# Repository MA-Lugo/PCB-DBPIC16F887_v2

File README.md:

# PCB-DBPIC16F887_v2
Development Board based on Microchip PIC16F887 8-Bit MCU

_Tarjeta de desarrollo basada en PIC16F887 (sistema mínimo)_

## Comenzando 🚀
### Pre-requisitos 📋

* Autodesk Eagle

## Wiki 📖

Puedes encontrar el esquemático [aquí.](https://drive.google.com/uc?export=view&id=1uyhpvZt8SFJf6NlxQCLjJcooKPEDv15b)

Tambíen puedes ver una animación [aquí.](https://drive.google.com/file/d/1NO_eVydhyPA-O2Zp3BOySrAR04YveleB/view?usp=sharing)

## Lista de Componentes 📖

## Ensable 🛠️

## Autor ✒️

* **Mario A. Lugo**  [MA-Lugo](https://github.com/MA-Lugo)

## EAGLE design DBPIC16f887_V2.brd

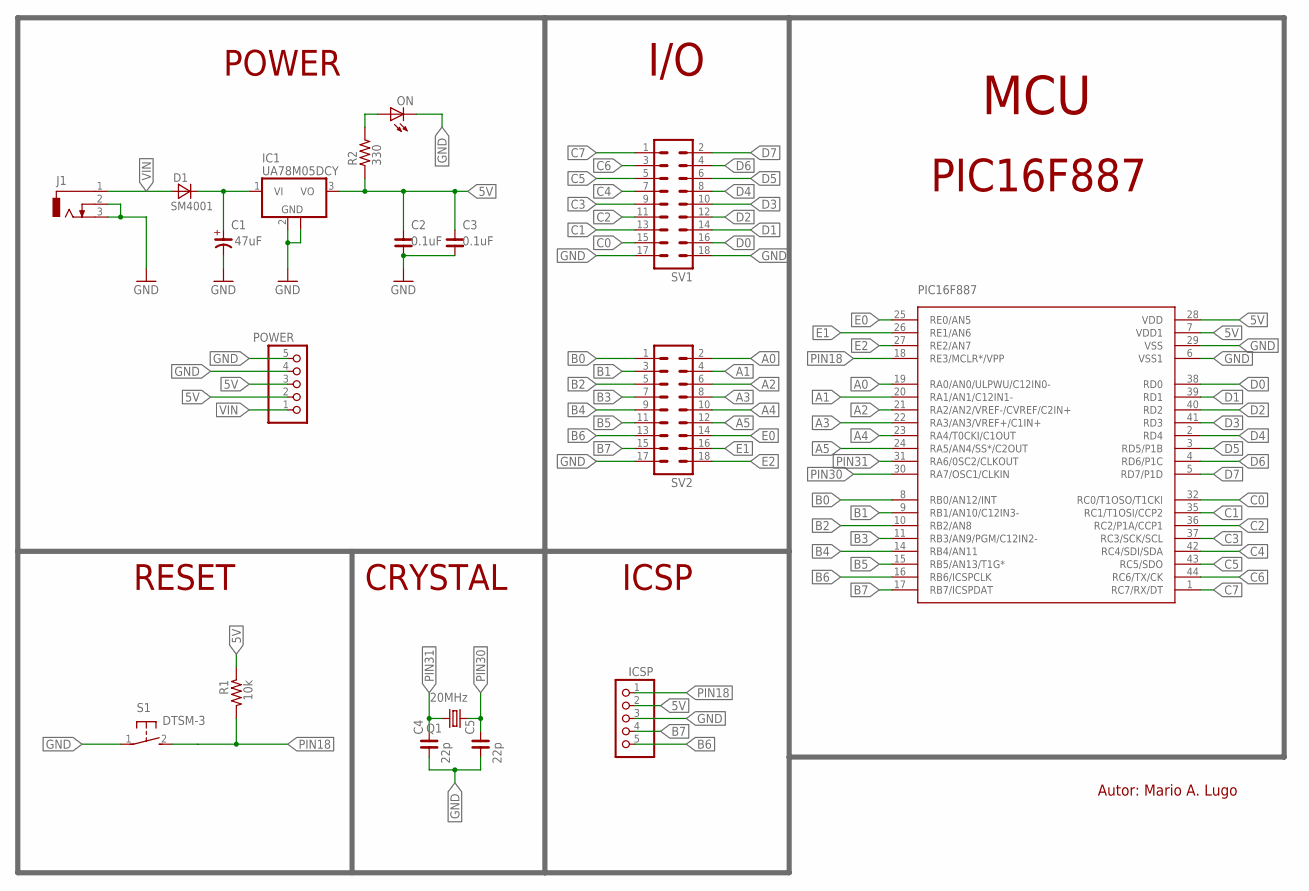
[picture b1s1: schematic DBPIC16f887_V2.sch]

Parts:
C1: 47uF; CSV-B
C2, C3: 0.1uF; C0805
C4, C5: 22p; C0805
D1: SM4001; MELF-MLL41
IC1: UA78M05DCY; SOT223
ICSP: 1X05
J1: DCJ0303
MCU: PIC16F887; TQFP44
ON: LEDCHIPLED_0805; CHIPLED_0805
POWER: PINHD-1X5; 1X05
Q1: 20MHz; CSM-7X-DU
R1: 10k; R0805
R2: 330; R0805
S1: DTSM-3
SV1, SV2: MA09-2

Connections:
5V: C2.2, C3.2, IC1.3 (VO), ICSP.2, MCU.7 (VDD1), MCU.28 (VDD), POWER.2, POWER.3, R1.1, R2.1
A0: MCU.19 (RA0/AN0/ULPWU/C12IN0-), SV2.2
A1: MCU.20 (RA1/AN1/C12IN1-), SV2.4
A2: MCU.21 (RA2/AN2/VREF-/CVREF/C2IN+), SV2.6
A3: MCU.22 (RA3/AN3/VREF+/C1IN+), SV2.8
A4: MCU.23 (RA4/T0CKI/C1OUT), SV2.10
A5: MCU.24 (RA5/AN4/SS*/C2OUT), SV2.12
B0: MCU.8 (RB0/AN12/INT), SV2.1
B1: MCU.9 (RB1/AN10/C12IN3-), SV2.3
B2: MCU.10 (RB2/AN8), SV2.5
B3: MCU.11 (RB3/AN9/PGM/C12IN2-), SV2.7
B4: MCU.14 (RB4/AN11), SV2.9
B5: MCU.15 (RB5/AN13/T1G*), SV2.11
B6: ICSP.5, MCU.16 (RB6/ICSPCLK), SV2.13
B7: ICSP.4, MCU.17 (RB7/ICSPDAT), SV2.15
C0: MCU.32 (RC0/T1OSO/T1CKI), SV1.15
C1: MCU.35 (RC1/T1OSI/CCP2), SV1.13
C2: MCU.36 (RC2/P1A/CCP1), SV1.11
C3: MCU.37 (RC3/SCK/SCL), SV1.9
C4: MCU.42 (RC4/SDI/SDA), SV1.7
C5: MCU.43 (RC5/SDO), SV1.5
C6: MCU.44 (RC6/TX/CK), SV1.3
C7: MCU.1 (RC7/RX/DT), SV1.1
D0: MCU.38 (RD0), SV1.16
D1: MCU.39 (RD1), SV1.14
D2: MCU.40 (RD2), SV1.12
D3: MCU.41 (RD3), SV1.10
D4: MCU.2 (RD4), SV1.8
D5: MCU.3 (RD5/P1B), SV1.6
D6: MCU.4 (RD6/P1C), SV1.4
D7: MCU.5 (RD7/P1D), SV1.2
E0: MCU.25 (RE0/AN5), SV2.14
E1: MCU.26 (RE1/AN6), SV2.16
E2: MCU.27 (RE2/AN7), SV2.18
GND: C1.-, C2.1, C3.1, C4.1, C5.1, IC1.2 (GND), IC1.4 (GND), ICSP.3, J1.2, J1.3, MCU.6 (VSS1), MCU.29 (VSS), ON.C, POWER.4, POWER.5, S1.1, SV1.17, SV1.18, SV2.17
LED1: ON.A, R2.2
PIN18: ICSP.1, MCU.18 (RE3/MCLR*/VPP), R1.2, S1.2
PIN30: C5.2, MCU.30 (RA7/OSC1/CLKIN), Q1.1
PIN31: C4.2, MCU.31 (RA6/0SC2/CLKOUT), Q1.2
VI: C1.+, D1.C, IC1.1 (VI)
VIN: D1.A, J1.1, POWER.1

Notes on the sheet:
POWER
CRYSTAL
RESET
ICSP
PIC16F887
MCU
I/O
Autor: Mario A. Lugo

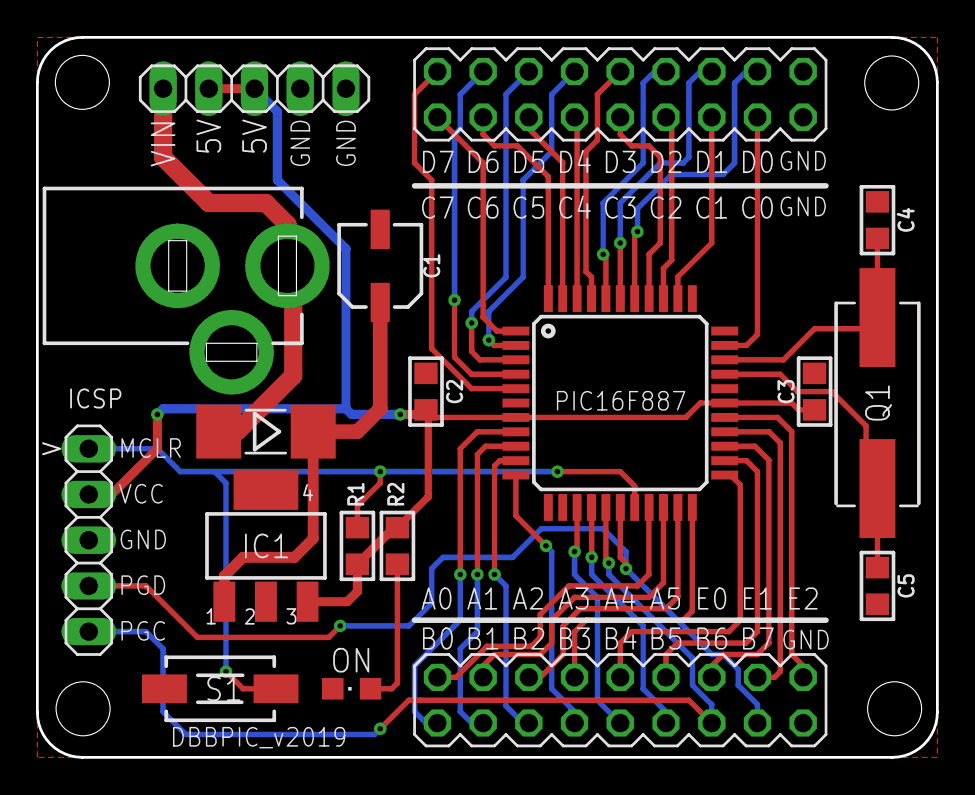
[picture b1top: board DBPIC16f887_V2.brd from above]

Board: 2 copper layers, 50.0 x 40.0 mm, 18 parts (0 on the bottom side), 41 nets.

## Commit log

2021-02-06 Uptdate files
2021-02-06 update img

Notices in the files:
parts and their libraries:
rc-master-smd: Copyright (C) 2007, Bob Starr
